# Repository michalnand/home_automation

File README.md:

# home_automation

crontab -e
@reboot sh /home/michal/projects/home_automation/src/launcher.sh

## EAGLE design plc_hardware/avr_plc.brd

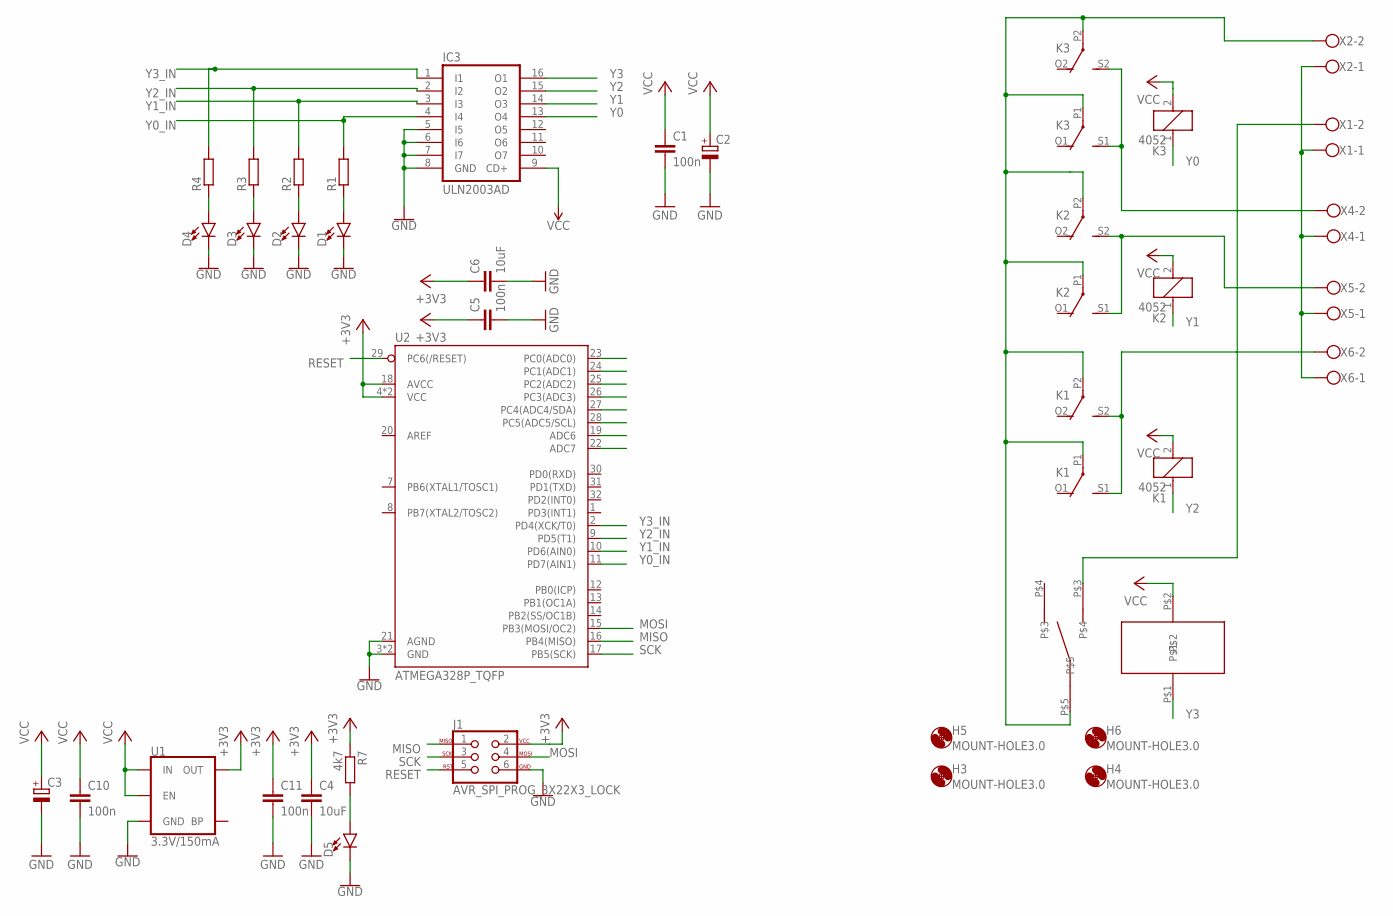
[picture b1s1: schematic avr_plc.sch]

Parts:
C1, C5, C10, C11: 100n; C0805
C2, C3: CPOL-EU153CLV-0810; 153CLV-0810
C4, C6: 10uF; C0805
D1, D2, D3, D4, D5: LED1206; LED-1206
H3, H4, H5, H6: MOUNT-HOLE3.0; 3,0
IC3: ULN2003AD; SO16
J1: AVR_SPI_PROG_3X22X3_LOCK; 2X3_LOCK
K1, K2, K3: 4052; F4052
R1, R2, R3, R4: R-EU_R0805; R0805
R7: 4k7; M0805
U1: 3.3V/150mA; SOT23-5
U2: ATMEGA328P_TQFP; TQFP32-08
U$1: T9G_RELAY
X1, X2: W239-302
X4, X5, X6: W237-102

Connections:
+3V3: C4.1, C5.1, C6.1, C11.1, J1.2, R7.1, U1.5 (OUT), U2.4 (VCC), U2.6 (VCC), U2.18 (AVCC)
GND: C1.2, C2.-, C3.-, C4.2, C5.2, C6.2, C10.2, C11.2, D1.C, D2.C, D3.C, D4.C, D5.C, IC3.5 (I5), IC3.6 (I6), IC3.7 (I7), IC3.8 (GND), J1.6, U1.2 (GND), U2.3 (GND), U2.5 (GND), U2.21 (AGND)
MISO: J1.1, U2.16 (PB4(MISO))
MOSI: J1.4, U2.15 (PB3(MOSI/OC2))
unnamed: D1.A, R1.1
unnamed: D2.A, R2.1
unnamed: D3.A, R3.1
unnamed: D4.A, R4.1
unnamed: D5.A, R7.2
unnamed: K1.P1, K1.P2, K2.P1, K2.P2, K3.P1, K3.P2, U$1.P$5, X2.2
unnamed: U$1.P$3, X1.2
unnamed: X1.1, X2.1, X4.1, X5.1, X6.1
unnamed: K1.S1 (S), K1.S2 (S), X6.2
unnamed: K2.S1 (S), K2.S2 (S), X5.2
unnamed: K3.S1 (S), K3.S2 (S), X4.2
RESET: J1.5, U2.29 (PC6(/RESET))
SCK: J1.3, U2.17 (PB5(SCK))
VCC: C1.1, C2.+, C3.+, C10.1, IC3.9 (CD+), K1.2, K2.2, K3.2, U1.1 (IN), U1.3 (EN), U$1.P$2
Y0: IC3.13 (O4), K3.1
Y0_IN: IC3.4 (I4), R1.2, U2.11 (PD7(AIN1))
Y1: IC3.14 (O3), K2.1
Y1_IN: IC3.3 (I3), R2.2, U2.10 (PD6(AIN0))
Y2: IC3.15 (O2), K1.1
Y2_IN: IC3.2 (I2), R3.2, U2.9 (PD5(T1))
Y3: IC3.16 (O1), U$1.P$1
Y3_IN: IC3.1 (I1), R4.2, U2.2 (PD4(XCK/T0))

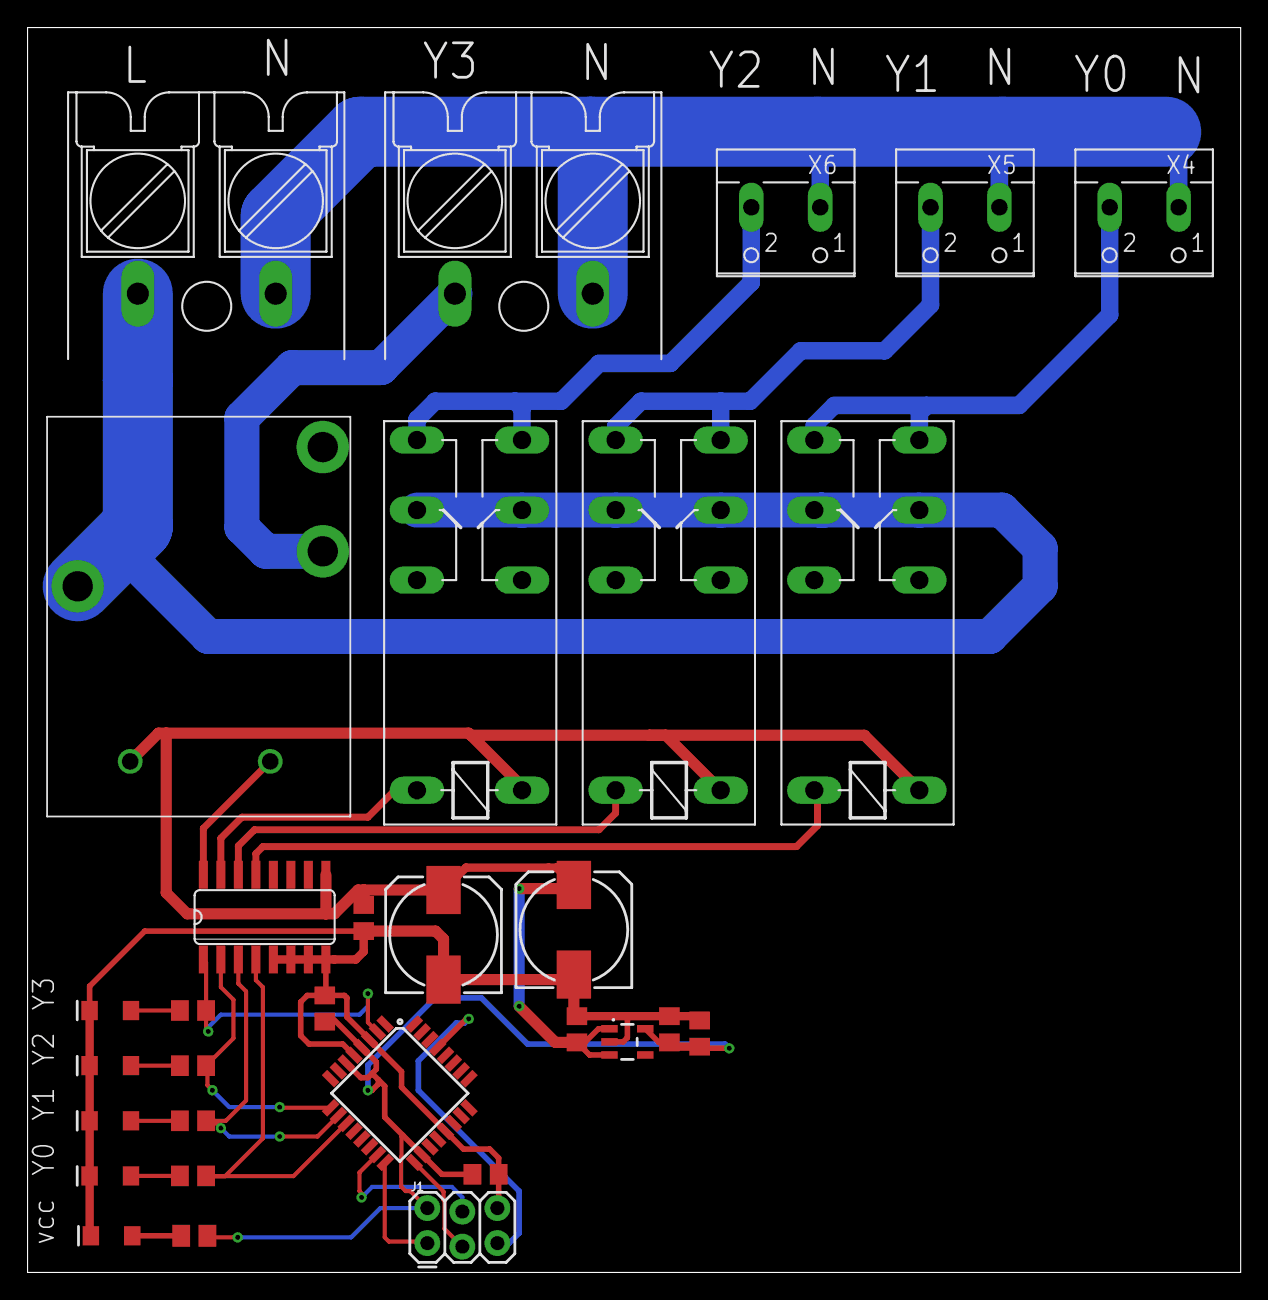
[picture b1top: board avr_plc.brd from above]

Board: 2 copper layers, 88.0 x 90.3 mm, 35 parts (0 on the bottom side), 26 nets.

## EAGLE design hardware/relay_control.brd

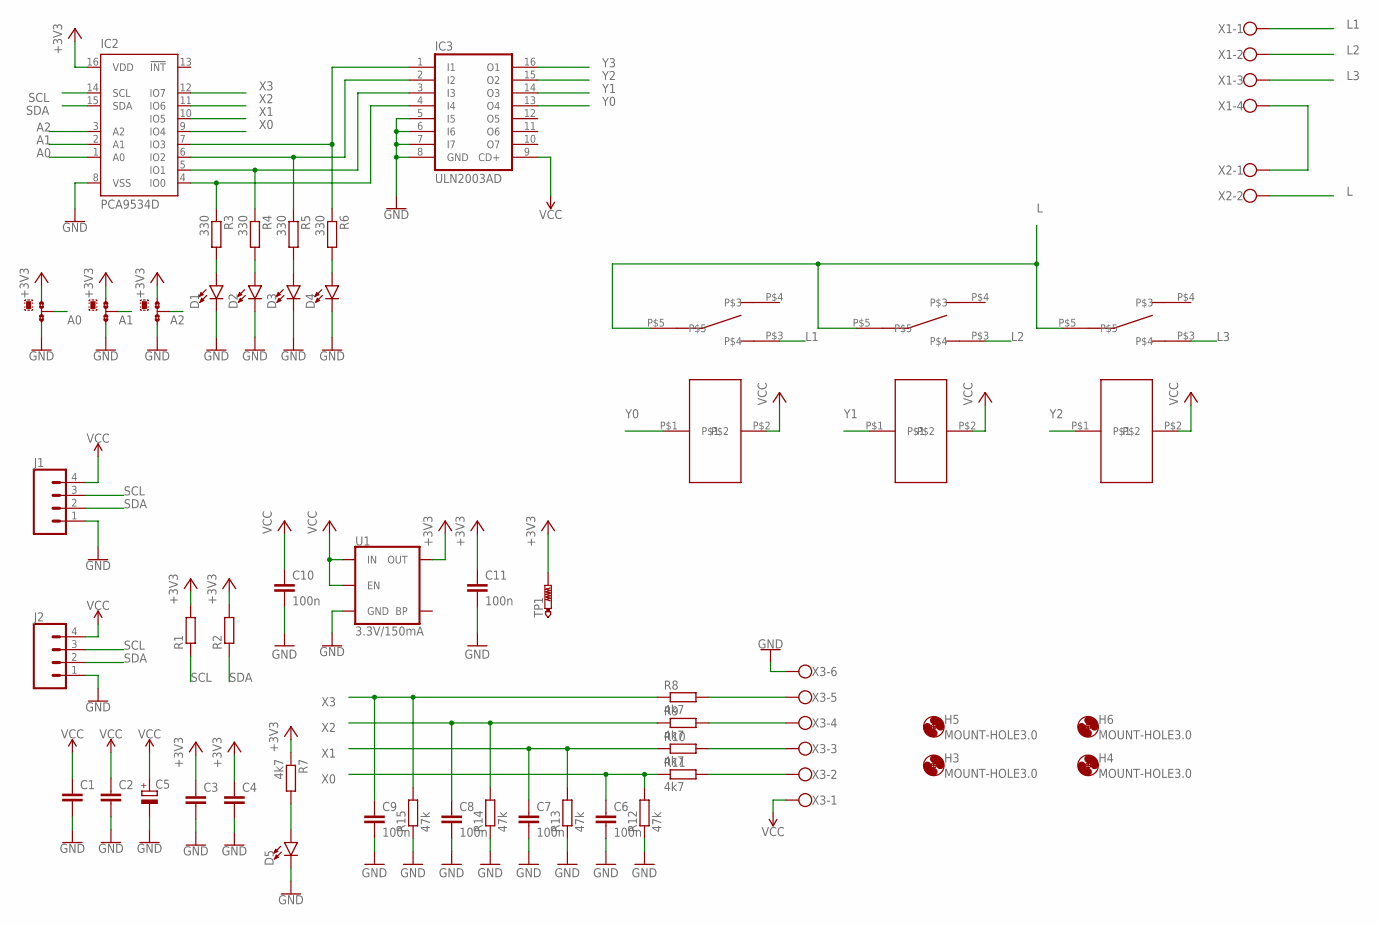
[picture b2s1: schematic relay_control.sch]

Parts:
C1, C2, C3, C4: C-EUC0805; C0805
C5: CPOL-EU150CLZ-1014; 150CLZ-1014
C6, C7, C8, C9, C10, C11: 100n; C0805
D1, D2, D3, D4, D5: LED1206; LED-1206
H3, H4, H5, H6: MOUNT-HOLE3.0; 3,0
IC2: PCA9534D; SO16W
IC3: ULN2003AD; SO16
J1, J2: CONN_04POLAR; MOLEX-1X4
JMP1, JMP2, JMP3: 0R-JUMPA; A0R-JMP
R1, R2: R-EU_M0805; M0805
R3, R4, R5, R6: 330; M0805
R7, R8, R9, R10, R11: 4k7; M0805
R12, R13, R14, R15: 47k; M0805
TP1: PTR1B2,54; B2,54
U1: 3.3V/150mA; SOT23-5
U$1, U$2, U$3: T9G_RELAY
X1: W239-104
X2: W239-302
X3: W237-6

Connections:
+3V3: C3.1, C4.1, C11.1, IC2.16 (VDD), JMP1.1, JMP2.1, JMP3.1, R1.2, R2.2, R7.1, TP1.TP, U1.5 (OUT)
A0: IC2.1 (A0), JMP1.2
A1: IC2.2 (A1), JMP2.2
A2: IC2.3 (A2), JMP3.2
GND: C1.2, C2.2, C3.2, C4.2, C5.-, C6.2, C7.2, C8.2, C9.2, C10.2, C11.2, D1.C, D2.C, D3.C, D4.C, D5.C, IC2.8 (VSS), IC3.5 (I5), IC3.6 (I6), IC3.7 (I7), IC3.8 (GND), J1.1, J2.1, JMP1.3, JMP2.3, JMP3.3, R12.1, R13.1, R14.1, R15.1, U1.2 (GND), X3.6
L: U$1.P$5, U$2.P$5, U$3.P$5, X2.2
L1: U$1.P$3, X1.1
L2: U$2.P$3, X1.2
L3: U$3.P$3, X1.3
unnamed: IC2.4 (IO0), IC3.4 (I4), R3.1
unnamed: D1.A, R3.2
unnamed: IC2.5 (IO1), IC3.3 (I3), R4.1
unnamed: D2.A, R4.2
unnamed: IC2.6 (IO2), IC3.2 (I2), R5.1
unnamed: D3.A, R5.2
unnamed: IC2.7 (IO3), IC3.1 (I1), R6.1
unnamed: D4.A, R6.2
unnamed: D5.A, R7.2
unnamed: X1.4, X2.1
unnamed: R11.2, X3.2
unnamed: R10.2, X3.3
unnamed: R9.2, X3.4
unnamed: R8.2, X3.5
SCL: IC2.14 (SCL), J1.3, J2.3, R1.1
SDA: IC2.15 (SDA), J1.2, J2.2, R2.1
VCC: C1.1, C2.1, C5.+, C10.1, IC3.9 (CD+), J1.4, J2.4, U1.1 (IN), U1.3 (EN), U$1.P$2, U$2.P$2, U$3.P$2, X3.1
X0: C6.1, IC2.9 (IO4), R11.1, R12.2
X1: C7.1, IC2.10 (IO5), R10.1, R13.2
X2: C8.1, IC2.11 (IO6), R9.1, R14.2
X3: C9.1, IC2.12 (IO7), R8.1, R15.2
Y0: IC3.13 (O4), U$1.P$1
Y1: IC3.14 (O3), U$2.P$1
Y2: IC3.15 (O2), U$3.P$1
Y3: IC3.16 (O1)

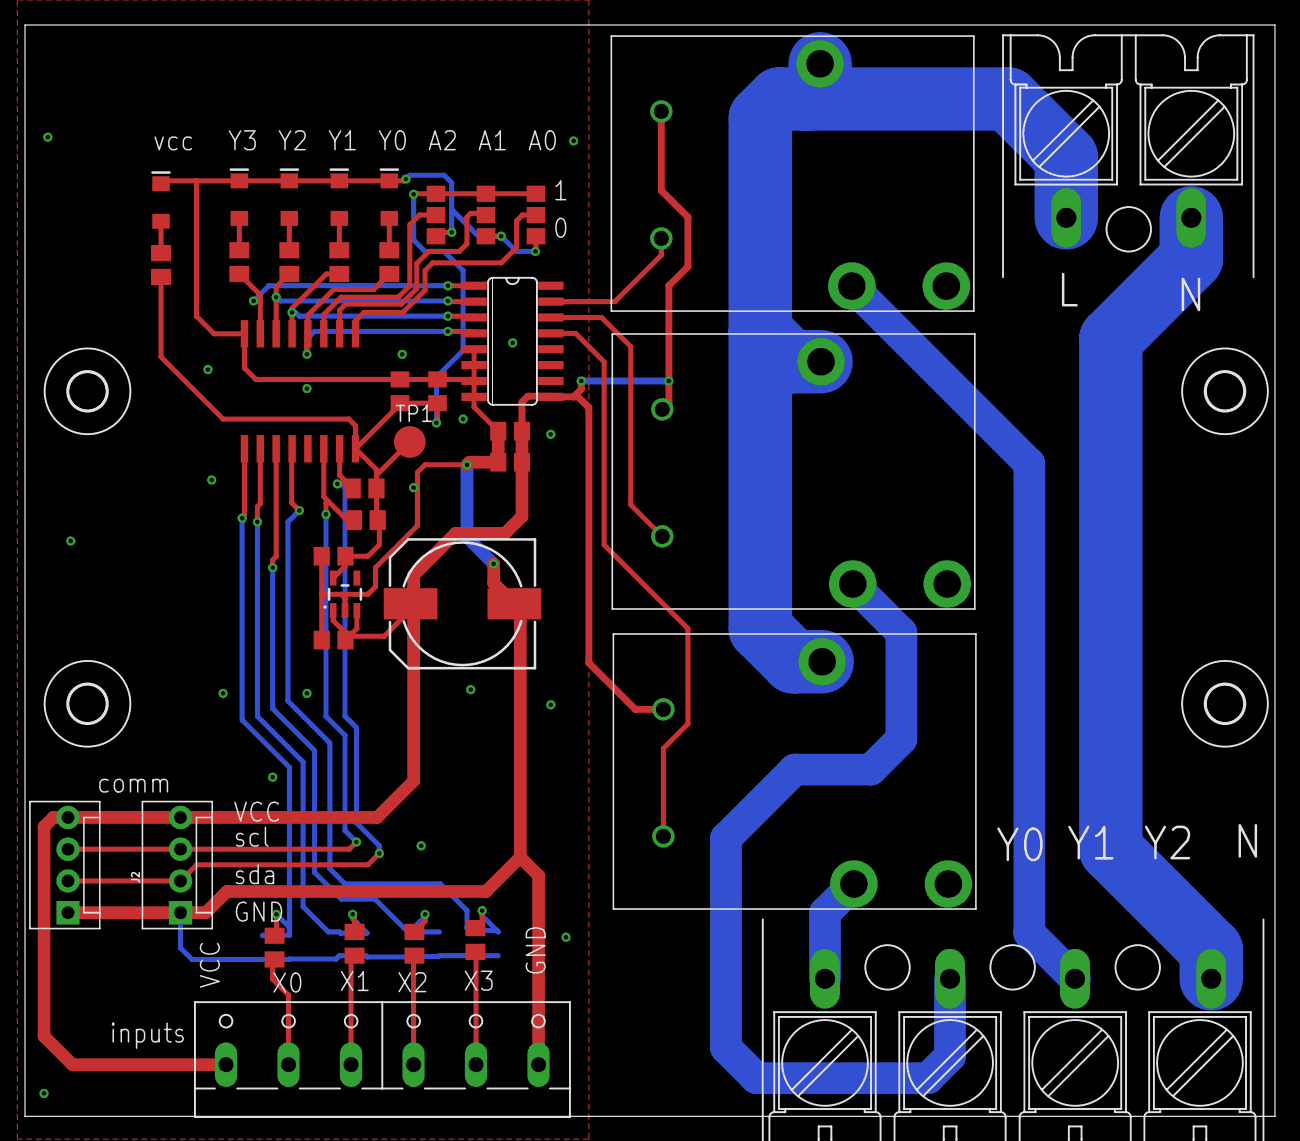
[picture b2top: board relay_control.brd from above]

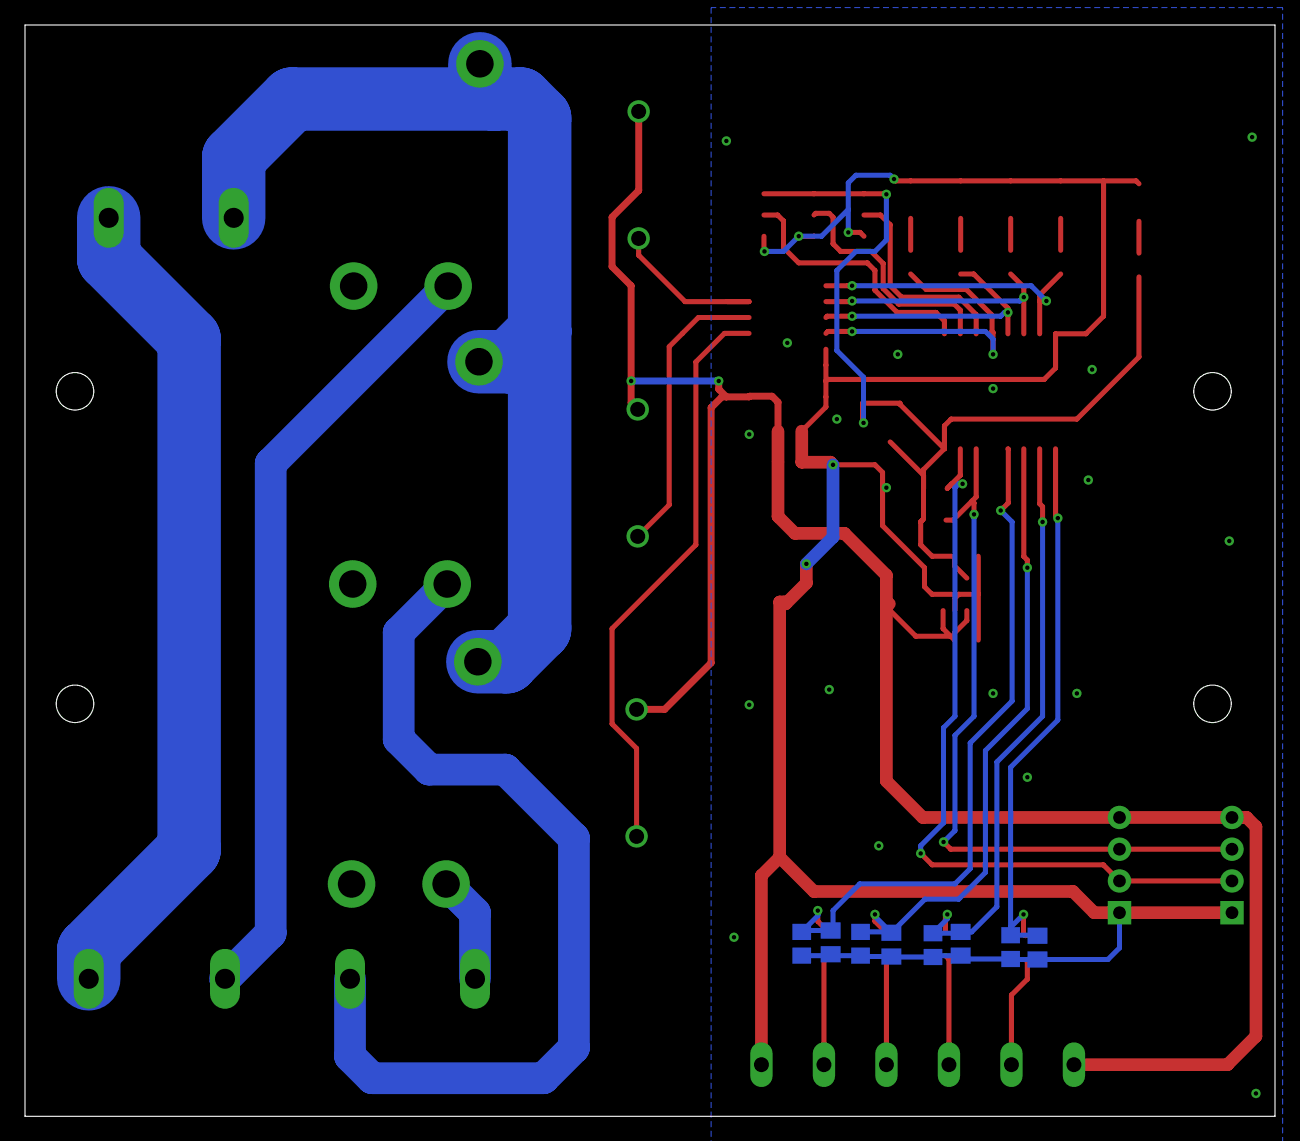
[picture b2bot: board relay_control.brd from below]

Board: 2 copper layers, 100.0 x 87.3 mm, 50 parts (8 on the bottom side), 33 nets.

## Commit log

2024-01-13 initial
2024-01-26 logging + cleaned up
2024-01-27 kalman soc predictor
2024-03-08 error handling
2024-04-03 logger
2025-02-19 hardware io check
2025-08-12 api changed
2026-06-06 api updated
2026-06-06 web app added
2026-06-06 page updated

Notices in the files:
parts and their libraries:
SparkFun-Connectors: Licensing: Creative Commons ShareAlike 4.0 International - https://creativecommons.org/licenses/by-sa/4.0
